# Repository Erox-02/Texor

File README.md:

# Texor
My ultra cool rust based keyboard

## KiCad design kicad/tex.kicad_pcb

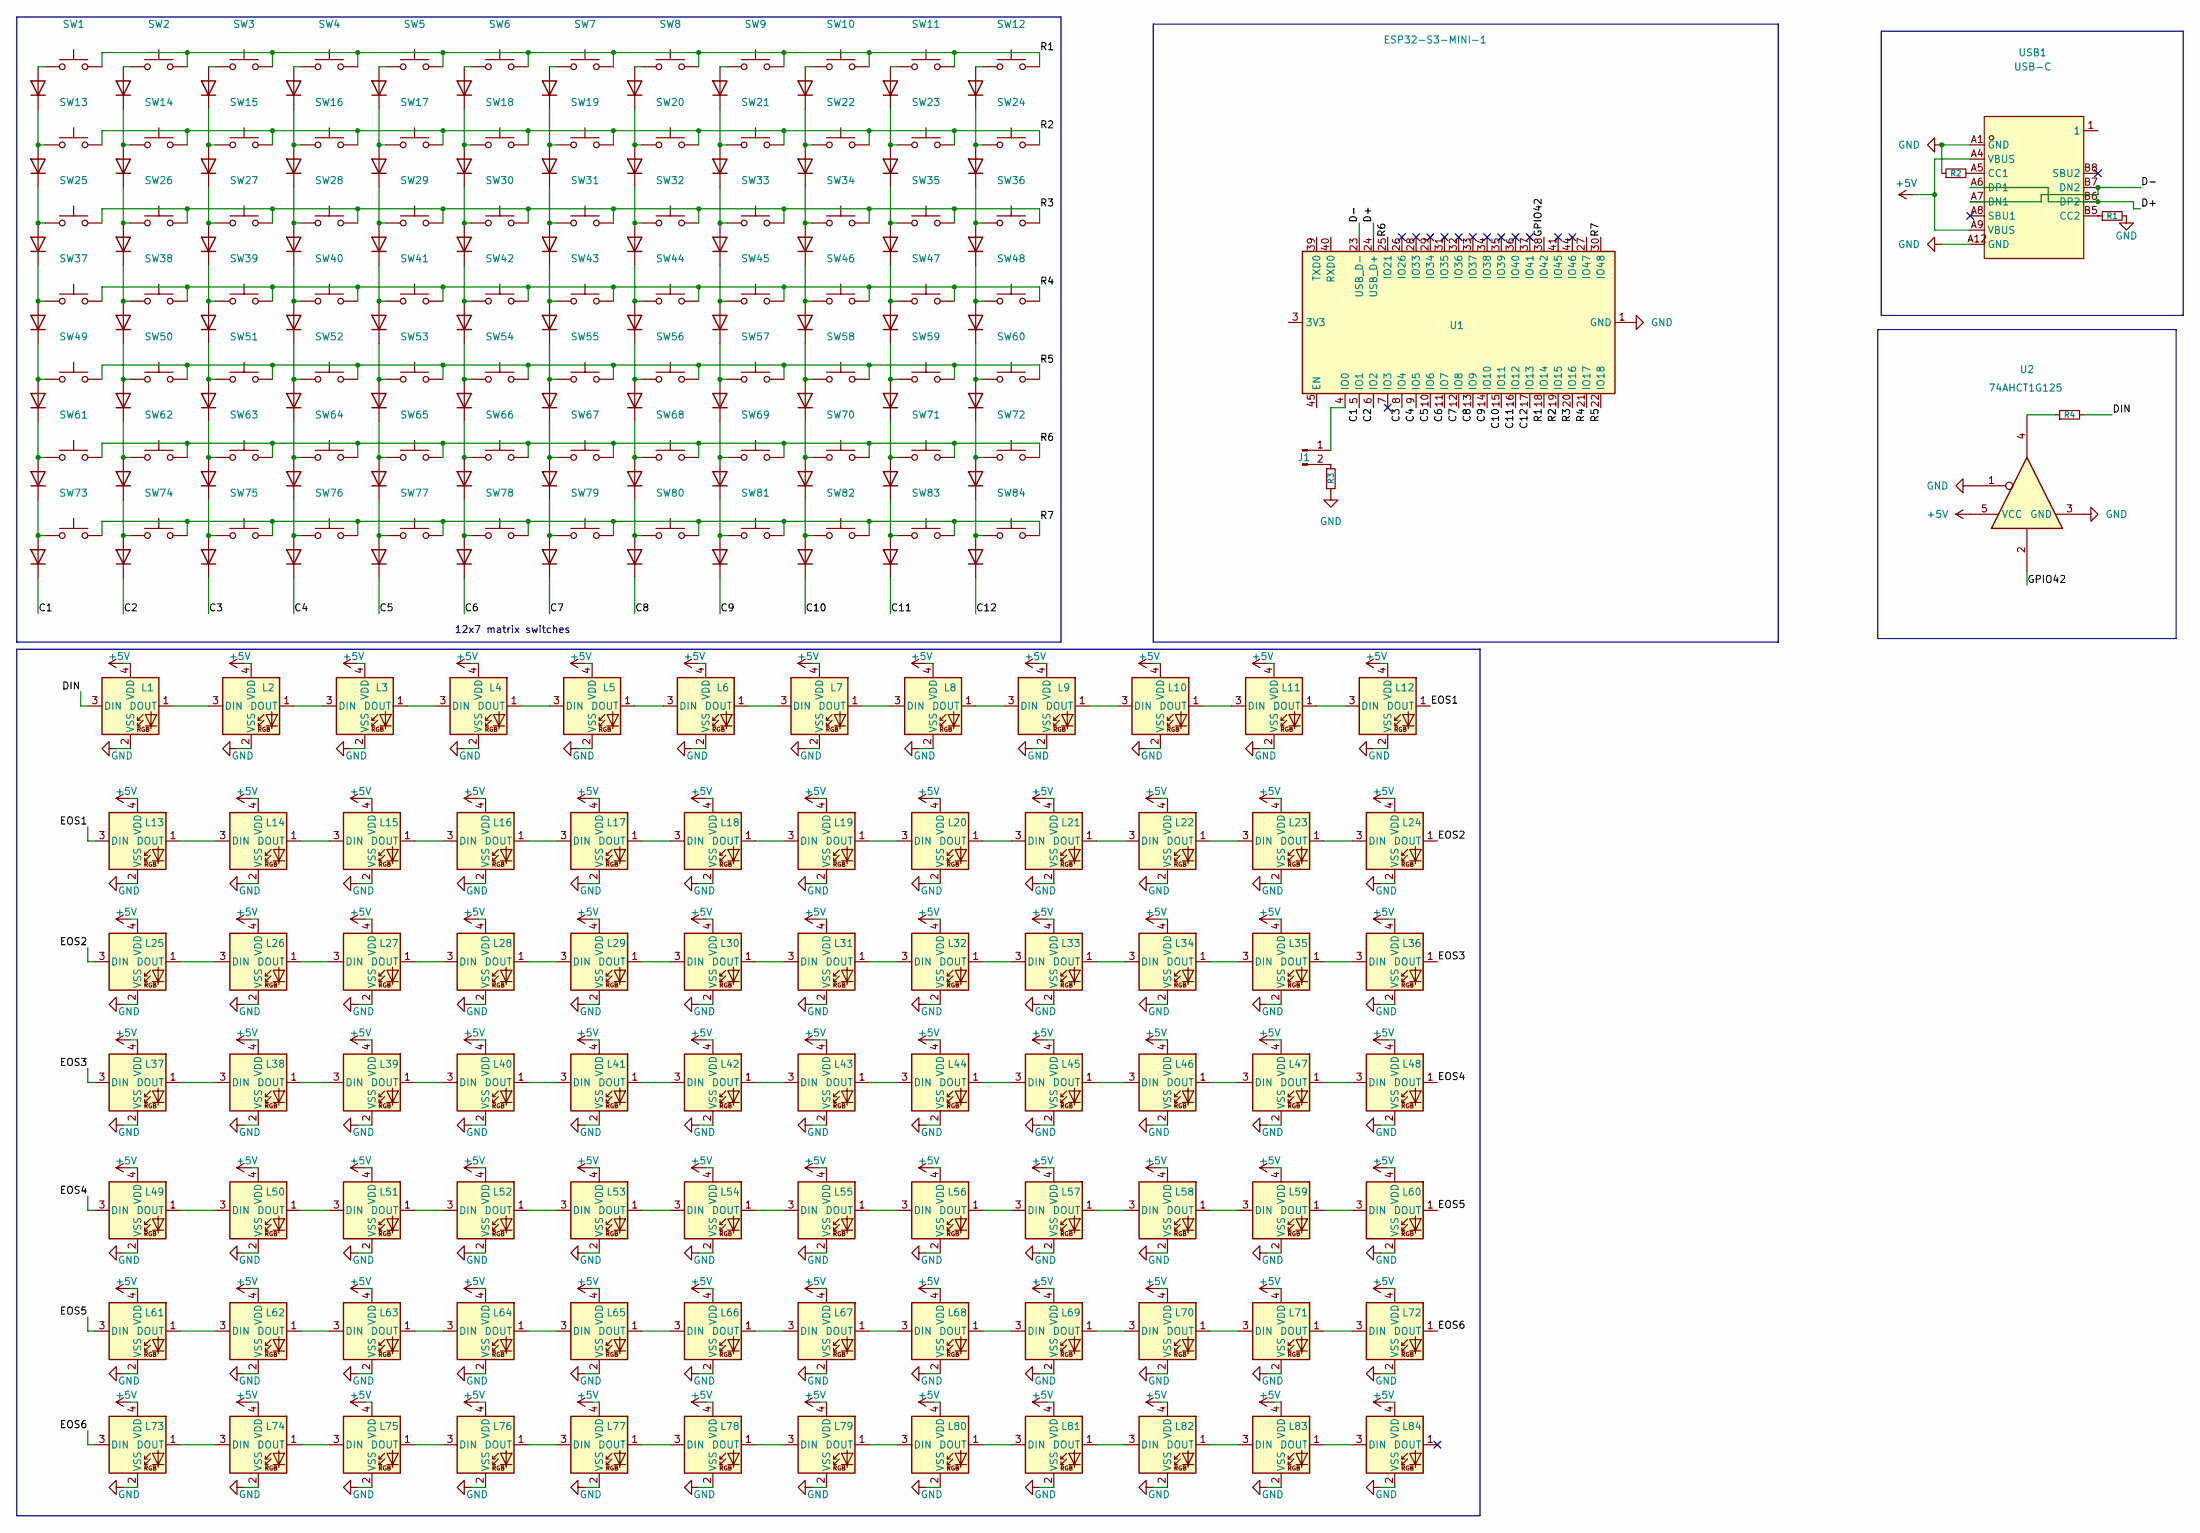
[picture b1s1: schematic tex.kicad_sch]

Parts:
D1, D2, D3, D4, D5, D6, D7, D8, D9, D10, D11, D12, D13, D14, D15, D16, D17, D18, D19, D20, D21, D22, D23, D24, D25, D26, D27, D28, D29, D30, D31, D32, D33, D34, D35, D36, D37, D38, D39, D40, D41, D42, D43, D44, D45, D46, D47, D48, D49, D50, D51, D52, D53, D54, D55, D56, D57, D58, D59, D60, D61, D62, D63, D64, D65, D66, D67, D68, D69, D70, D71, D72, D73, D74, D75, D76, D77, D78, D79, D80, D81, D82, D83, D84: 1N4148W; D_SOD-123
J1: Testpoint; PinSocket_1x02_P2.00mm_Vertical
L1, L2, L3, L4, L5, L6, L7, L8, L9, L10, L11, L12, L13, L14, L15, L16, L17, L18, L19, L20, L21, L22, L23, L24, L25, L26, L27, L28, L29, L30, L31, L32, L33, L34, L35, L36, L37, L38, L39, L40, L41, L42, L43, L44, L45, L46, L47, L48, L49, L50, L51, L52, L53, L54, L55, L56, L57, L58, L59, L60, L61, L62, L63, L64, L65, L66, L67, L68, L69, L70, L71, L72, L73, L74, L75, L76, L77, L78, L79, L80, L81, L82, L83, L84: WS2812B-2020; LED_WS2812B-2020_PLCC4_2.0x2.0mm
R1, R2: 5.1k; R_0603_1608Metric
R3: 10k; R_0603_1608Metric
R4: 220 ohm; R_0603_1608Metric
SW1, SW2, SW3, SW4, SW5, SW6, SW7, SW8, SW9, SW10, SW11, SW12, SW13, SW14, SW15, SW16, SW17, SW18, SW19, SW20, SW21, SW22, SW23, SW24, SW25, SW26, SW27, SW28, SW29, SW30, SW31, SW32, SW33, SW34, SW35, SW36, SW37, SW38, SW39, SW40, SW41, SW42, SW43, SW44, SW45, SW46, SW47, SW48, SW49, SW50, SW51, SW52, SW53, SW54, SW55, SW56, SW57, SW58, SW59, SW60, SW61, SW62, SW63, SW64, SW65, SW66, SW67, SW68, SW69, SW70, SW71, SW72, SW73, SW74, SW75, SW76, SW77, SW78, SW79, SW80, SW81, SW82, SW83, SW84: SW_Push; SW_Cherry_MX_1.00u_PCB
U1: ESP32-S3-MINI-1; ESP32-S2-MINI-1
U2: 74AHCT1G125; SOT-353_SC-70-5
USB1: USB-C; USB-C-SMD_TYPE-C-31-M-31; MPN TYPE-C-31-M-31; LCSC Part C2760486

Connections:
+5V: L1.4 (VDD), L2.4 (VDD), L3.4 (VDD), L4.4 (VDD), L5.4 (VDD), L6.4 (VDD), L7.4 (VDD), L8.4 (VDD), L9.4 (VDD), L10.4 (VDD), L11.4 (VDD), L12.4 (VDD), L13.4 (VDD), L14.4 (VDD), L15.4 (VDD), L16.4 (VDD), L17.4 (VDD), L18.4 (VDD), L19.4 (VDD), L20.4 (VDD), L21.4 (VDD), L22.4 (VDD), L23.4 (VDD), L24.4 (VDD), L25.4 (VDD), L26.4 (VDD), L27.4 (VDD), L28.4 (VDD), L29.4 (VDD), L30.4 (VDD), L31.4 (VDD), L32.4 (VDD), L33.4 (VDD), L34.4 (VDD), L35.4 (VDD), L36.4 (VDD), L37.4 (VDD), L38.4 (VDD), L39.4 (VDD), L40.4 (VDD), L41.4 (VDD), L42.4 (VDD), L43.4 (VDD), L44.4 (VDD), L45.4 (VDD), L46.4 (VDD), L47.4 (VDD), L48.4 (VDD), L49.4 (VDD), L50.4 (VDD), L51.4 (VDD), L52.4 (VDD), L53.4 (VDD), L54.4 (VDD), L55.4 (VDD), L56.4 (VDD), L57.4 (VDD), L58.4 (VDD), L59.4 (VDD), L60.4 (VDD), L61.4 (VDD), L62.4 (VDD), L63.4 (VDD), L64.4 (VDD), L65.4 (VDD), L66.4 (VDD), L67.4 (VDD), L68.4 (VDD), L69.4 (VDD), L70.4 (VDD), L71.4 (VDD), L72.4 (VDD), L73.4 (VDD), L74.4 (VDD), L75.4 (VDD), L76.4 (VDD), L77.4 (VDD), L78.4 (VDD), L79.4 (VDD), L80.4 (VDD), L81.4 (VDD), L82.4 (VDD), L83.4 (VDD), L84.4 (VDD), U2.5 (VCC), USB1.A4 (VBUS), USB1.A9 (VBUS); also elsewhere on the board
/3.3v: U1.3 (3V3); also elsewhere on the board
/C1: D73.1 (K), U1.5 (IO1)
/C2: D74.1 (K), U1.6 (IO2)
/C3: D75.1 (K), U1.8 (IO4)
/C4: D76.1 (K), U1.9 (IO5)
/C5: D77.1 (K), U1.10 (IO6)
/C6: D78.1 (K), U1.11 (IO7)
/C7: D79.1 (K), U1.12 (IO8)
/C8: D80.1 (K), U1.13 (IO9)
/C9: D81.1 (K), U1.14 (IO10)
/C10: D82.1 (K), U1.15 (IO11)
/C11: D83.1 (K), U1.16 (IO12)
/C12: D84.1 (K), U1.17 (IO13)
/D+: U1.24 (USB_D+), USB1.A6 (DP1), USB1.B6 (DP2)
/D-: U1.23 (USB_D-), USB1.A7 (DN1), USB1.B7 (DN2)
/DIN: L1.3 (DIN), R4.2
/EOS1: L12.1 (DOUT), L13.3 (DIN)
/EOS2: L24.1 (DOUT), L25.3 (DIN)
/EOS3: L36.1 (DOUT), L37.3 (DIN)
/EOS4: L48.1 (DOUT), L49.3 (DIN)
/EOS5: L60.1 (DOUT), L61.3 (DIN)
/EOS6: L72.1 (DOUT), L73.3 (DIN)
/GPIO42: U1.38 (IO42), U2.2
/R1: SW1.2, SW2.2, SW3.2, SW4.2, SW5.2, SW6.2, SW7.2, SW8.2, SW9.2, SW10.2, SW11.2, SW12.2, U1.18 (IO14)
/R2: SW13.2, SW14.2, SW15.2, SW16.2, SW17.2, SW18.2, SW19.2, SW20.2, SW21.2, SW22.2, SW23.2, SW24.2, U1.19 (IO15)
/R3: SW25.2, SW26.2, SW27.2, SW28.2, SW29.2, SW30.2, SW31.2, SW32.2, SW33.2, SW34.2, SW35.2, SW36.2, U1.20 (IO16)
/R4: SW37.2, SW38.2, SW39.2, SW40.2, SW41.2, SW42.2, SW43.2, SW44.2, SW45.2, SW46.2, SW47.2, SW48.2, U1.21 (IO17)
/R5: SW49.2, SW50.2, SW51.2, SW52.2, SW53.2, SW54.2, SW55.2, SW56.2, SW57.2, SW58.2, SW59.2, SW60.2, U1.22 (IO18)
/R6: SW61.2, SW62.2, SW63.2, SW64.2, SW65.2, SW66.2, SW67.2, SW68.2, SW69.2, SW70.2, SW71.2, SW72.2, U1.25 (IO21)
/R7: SW73.2, SW74.2, SW75.2, SW76.2, SW77.2, SW78.2, SW79.2, SW80.2, SW81.2, SW82.2, SW83.2, SW84.2, U1.30 (IO48)
GND: L1.2 (VSS), L2.2 (VSS), L3.2 (VSS), L4.2 (VSS), L5.2 (VSS), L6.2 (VSS), L7.2 (VSS), L8.2 (VSS), L9.2 (VSS), L10.2 (VSS), L11.2 (VSS), L12.2 (VSS), L13.2 (VSS), L14.2 (VSS), L15.2 (VSS), L16.2 (VSS), L17.2 (VSS), L18.2 (VSS), L19.2 (VSS), L20.2 (VSS), L21.2 (VSS), L22.2 (VSS), L23.2 (VSS), L24.2 (VSS), L25.2 (VSS), L26.2 (VSS), L27.2 (VSS), L28.2 (VSS), L29.2 (VSS), L30.2 (VSS), L31.2 (VSS), L32.2 (VSS), L33.2 (VSS), L34.2 (VSS), L35.2 (VSS), L36.2 (VSS), L37.2 (VSS), L38.2 (VSS), L39.2 (VSS), L40.2 (VSS), L41.2 (VSS), L42.2 (VSS), L43.2 (VSS), L44.2 (VSS), L45.2 (VSS), L46.2 (VSS), L47.2 (VSS), L48.2 (VSS), L49.2 (VSS), L50.2 (VSS), L51.2 (VSS), L52.2 (VSS), L53.2 (VSS), L54.2 (VSS), L55.2 (VSS), L56.2 (VSS), L57.2 (VSS), L58.2 (VSS), L59.2 (VSS), L60.2 (VSS), L61.2 (VSS), L62.2 (VSS), L63.2 (VSS), L64.2 (VSS), L65.2 (VSS), L66.2 (VSS), L67.2 (VSS), L68.2 (VSS), L69.2 (VSS), L70.2 (VSS), L71.2 (VSS), L72.2 (VSS), L73.2 (VSS), L74.2 (VSS), L75.2 (VSS), L76.2 (VSS), L77.2 (VSS), L78.2 (VSS), L79.2 (VSS), L80.2 (VSS), L81.2 (VSS), L82.2 (VSS), L83.2 (VSS), L84.2 (VSS), R1.2, R2.1, R3.2, U1.1 (GND), U1.2 (GND), U1.42 (GND), U1.43 (GND), U1.46 (GND), U1.47 (GND), U1.48 (GND), U1.49 (GND), U1.50 (GND), U1.51 (GND), U1.52 (GND), U1.53 (GND), U1.54 (GND), U1.55 (GND), U1.56 (GND), U1.57 (GND), U1.58 (GND), U1.59 (GND), U1.60 (GND), U1.61 (GND), U1.62 (GND), U1.63 (GND), U1.64 (GND), U1.65 (GND), U2.1, U2.3 (GND), USB1.A1 (GND), USB1.A12 (GND); also elsewhere on the board
unnamed: D1.2 (A), SW1.1
unnamed: D1.1 (K), D13.2 (A), SW13.1
unnamed: D2.2 (A), SW2.1
unnamed: D3.2 (A), SW3.1
unnamed: D4.2 (A), SW4.1
unnamed: D5.2 (A), SW5.1
unnamed: D6.2 (A), SW6.1
unnamed: D7.2 (A), SW7.1
unnamed: D8.2 (A), SW8.1
unnamed: D9.2 (A), SW9.1
unnamed: D10.2 (A), SW10.1
unnamed: D10.1 (K), D22.2 (A), SW22.1
unnamed: D11.2 (A), SW11.1
unnamed: D11.1 (K), D23.2 (A), SW23.1
unnamed: D12.2 (A), SW12.1
unnamed: D12.1 (K), D24.2 (A), SW24.1
unnamed: D13.1 (K), D25.2 (A), SW25.1
unnamed: D2.1 (K), D14.2 (A), SW14.1
unnamed: D14.1 (K), D26.2 (A), SW26.1
unnamed: D3.1 (K), D15.2 (A), SW15.1
unnamed: D15.1 (K), D27.2 (A), SW27.1
unnamed: D4.1 (K), D16.2 (A), SW16.1
unnamed: D16.1 (K), D28.2 (A), SW28.1
unnamed: D5.1 (K), D17.2 (A), SW17.1
unnamed: D17.1 (K), D29.2 (A), SW29.1
unnamed: D6.1 (K), D18.2 (A), SW18.1
unnamed: D18.1 (K), D30.2 (A), SW30.1
unnamed: D7.1 (K), D19.2 (A), SW19.1
unnamed: D19.1 (K), D31.2 (A), SW31.1
unnamed: D8.1 (K), D20.2 (A), SW20.1
unnamed: D20.1 (K), D32.2 (A), SW32.1
unnamed: D9.1 (K), D21.2 (A), SW21.1
unnamed: D21.1 (K), D33.2 (A), SW33.1
unnamed: D22.1 (K), D34.2 (A), SW34.1
unnamed: D23.1 (K), D35.2 (A), SW35.1
unnamed: D24.1 (K), D36.2 (A), SW36.1
unnamed: D25.1 (K), D37.2 (A), SW37.1
unnamed: D26.1 (K), D38.2 (A), SW38.1
unnamed: D27.1 (K), D39.2 (A), SW39.1
unnamed: D28.1 (K), D40.2 (A), SW40.1
unnamed: D29.1 (K), D41.2 (A), SW41.1
unnamed: D30.1 (K), D42.2 (A), SW42.1
unnamed: D31.1 (K), D43.2 (A), SW43.1
unnamed: D32.1 (K), D44.2 (A), SW44.1
unnamed: D33.1 (K), D45.2 (A), SW45.1
unnamed: D34.1 (K), D46.2 (A), SW46.1
unnamed: D35.1 (K), D47.2 (A), SW47.1
unnamed: D36.1 (K), D48.2 (A), SW48.1
unnamed: D37.1 (K), D49.2 (A), SW49.1
unnamed: D38.1 (K), D50.2 (A), SW50.1
unnamed: D39.1 (K), D51.2 (A), SW51.1
unnamed: D40.1 (K), D52.2 (A), SW52.1
unnamed: D41.1 (K), D53.2 (A), SW53.1
unnamed: D42.1 (K), D54.2 (A), SW54.1
unnamed: D43.1 (K), D55.2 (A), SW55.1
unnamed: D44.1 (K), D56.2 (A), SW56.1
unnamed: D45.1 (K), D57.2 (A), SW57.1
unnamed: D46.1 (K), D58.2 (A), SW58.1
unnamed: D47.1 (K), D59.2 (A), SW59.1
unnamed: D48.1 (K), D60.2 (A), SW60.1
unnamed: D49.1 (K), D61.2 (A), SW61.1
unnamed: D50.1 (K), D62.2 (A), SW62.1
unnamed: D51.1 (K), D63.2 (A), SW63.1
unnamed: D52.1 (K), D64.2 (A), SW64.1
unnamed: D53.1 (K), D65.2 (A), SW65.1
unnamed: D54.1 (K), D66.2 (A), SW66.1
unnamed: D55.1 (K), D67.2 (A), SW67.1
unnamed: D56.1 (K), D68.2 (A), SW68.1
unnamed: D57.1 (K), D69.2 (A), SW69.1
unnamed: D58.1 (K), D70.2 (A), SW70.1
unnamed: D59.1 (K), D71.2 (A), SW71.1
unnamed: D60.1 (K), D72.2 (A), SW72.1
unnamed: D61.1 (K), D73.2 (A), SW73.1
unnamed: D62.1 (K), D74.2 (A), SW74.1
unnamed: D63.1 (K), D75.2 (A), SW75.1
unnamed: D64.1 (K), D76.2 (A), SW76.1
unnamed: D65.1 (K), D77.2 (A), SW77.1
unnamed: D66.1 (K), D78.2 (A), SW78.1
unnamed: D67.1 (K), D79.2 (A), SW79.1
unnamed: D68.1 (K), D80.2 (A), SW80.1
unnamed: D69.1 (K), D81.2 (A), SW81.1
unnamed: D70.1 (K), D82.2 (A), SW82.1
unnamed: D71.1 (K), D83.2 (A), SW83.1
unnamed: D72.1 (K), D84.2 (A), SW84.1
unnamed: J1.1, U1.4 (IO0)
unnamed: J1.2, R3.1
unnamed: L1.1 (DOUT), L2.3 (DIN)
unnamed: L2.1 (DOUT), L3.3 (DIN)
unnamed: L3.1 (DOUT), L4.3 (DIN)
unnamed: L4.1 (DOUT), L5.3 (DIN)
unnamed: L5.1 (DOUT), L6.3 (DIN)
unnamed: L6.1 (DOUT), L7.3 (DIN)
unnamed: L7.1 (DOUT), L8.3 (DIN)
unnamed: L8.1 (DOUT), L9.3 (DIN)
unnamed: L9.1 (DOUT), L10.3 (DIN)
unnamed: L10.1 (DOUT), L11.3 (DIN)
unnamed: L11.1 (DOUT), L12.3 (DIN)
unnamed: L13.1 (DOUT), L14.3 (DIN)
unnamed: L14.1 (DOUT), L15.3 (DIN)
unnamed: L15.1 (DOUT), L16.3 (DIN)
unnamed: L16.1 (DOUT), L17.3 (DIN)
unnamed: L17.1 (DOUT), L18.3 (DIN)
unnamed: L18.1 (DOUT), L19.3 (DIN)
unnamed: L19.1 (DOUT), L20.3 (DIN)
unnamed: L20.1 (DOUT), L21.3 (DIN)
unnamed: L21.1 (DOUT), L22.3 (DIN)
unnamed: L22.1 (DOUT), L23.3 (DIN)
unnamed: L23.1 (DOUT), L24.3 (DIN)
unnamed: L25.1 (DOUT), L26.3 (DIN)
unnamed: L26.1 (DOUT), L27.3 (DIN)
unnamed: L27.1 (DOUT), L28.3 (DIN)
unnamed: L28.1 (DOUT), L29.3 (DIN)
unnamed: L29.1 (DOUT), L30.3 (DIN)
unnamed: L30.1 (DOUT), L31.3 (DIN)
unnamed: L31.1 (DOUT), L32.3 (DIN)
unnamed: L32.1 (DOUT), L33.3 (DIN)
unnamed: L33.1 (DOUT), L34.3 (DIN)
unnamed: L34.1 (DOUT), L35.3 (DIN)
unnamed: L35.1 (DOUT), L36.3 (DIN)
unnamed: L37.1 (DOUT), L38.3 (DIN)
unnamed: L38.1 (DOUT), L39.3 (DIN)
unnamed: L39.1 (DOUT), L40.3 (DIN)
unnamed: L40.1 (DOUT), L41.3 (DIN)
unnamed: L41.1 (DOUT), L42.3 (DIN)
unnamed: L42.1 (DOUT), L43.3 (DIN)
unnamed: L43.1 (DOUT), L44.3 (DIN)
unnamed: L44.1 (DOUT), L45.3 (DIN)
unnamed: L45.1 (DOUT), L46.3 (DIN)
unnamed: L46.1 (DOUT), L47.3 (DIN)
unnamed: L47.1 (DOUT), L48.3 (DIN)
unnamed: L49.1 (DOUT), L50.3 (DIN)
unnamed: L50.1 (DOUT), L51.3 (DIN)
unnamed: L51.1 (DOUT), L52.3 (DIN)
unnamed: L52.1 (DOUT), L53.3 (DIN)
unnamed: L53.1 (DOUT), L54.3 (DIN)
unnamed: L54.1 (DOUT), L55.3 (DIN)
unnamed: L55.1 (DOUT), L56.3 (DIN)
unnamed: L56.1 (DOUT), L57.3 (DIN)
unnamed: L57.1 (DOUT), L58.3 (DIN)
unnamed: L58.1 (DOUT), L59.3 (DIN)
unnamed: L59.1 (DOUT), L60.3 (DIN)
unnamed: L61.1 (DOUT), L62.3 (DIN)
unnamed: L62.1 (DOUT), L63.3 (DIN)
unnamed: L63.1 (DOUT), L64.3 (DIN)
unnamed: L64.1 (DOUT), L65.3 (DIN)
unnamed: L65.1 (DOUT), L66.3 (DIN)
unnamed: L66.1 (DOUT), L67.3 (DIN)
unnamed: L67.1 (DOUT), L68.3 (DIN)
unnamed: L68.1 (DOUT), L69.3 (DIN)
unnamed: L69.1 (DOUT), L70.3 (DIN)
unnamed: L70.1 (DOUT), L71.3 (DIN)
unnamed: L71.1 (DOUT), L72.3 (DIN)
unnamed: L73.1 (DOUT), L74.3 (DIN)
unnamed: L74.1 (DOUT), L75.3 (DIN)
unnamed: L75.1 (DOUT), L76.3 (DIN)
unnamed: L76.1 (DOUT), L77.3 (DIN)
unnamed: L77.1 (DOUT), L78.3 (DIN)
unnamed: L78.1 (DOUT), L79.3 (DIN)
unnamed: L79.1 (DOUT), L80.3 (DIN)
unnamed: L80.1 (DOUT), L81.3 (DIN)
unnamed: L81.1 (DOUT), L82.3 (DIN)
unnamed: L82.1 (DOUT), L83.3 (DIN)
unnamed: L83.1 (DOUT), L84.3 (DIN)
unnamed: R4.1, U2.4
unnamed: R2.2, USB1.A5 (CC1)
unnamed: R1.1, USB1.B5 (CC2)

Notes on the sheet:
12x7 matrix switches

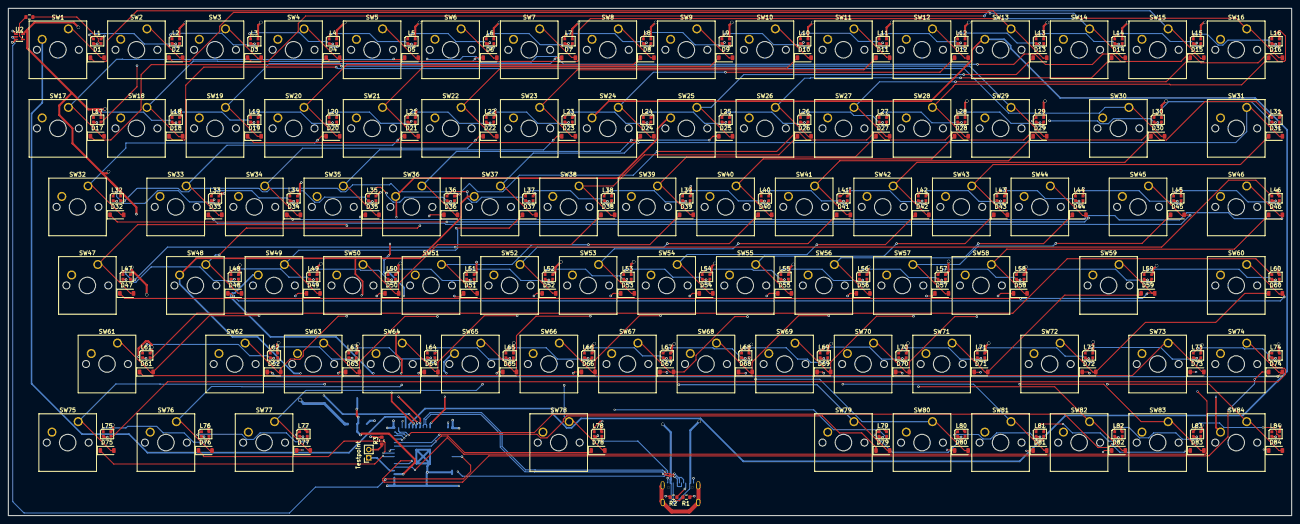
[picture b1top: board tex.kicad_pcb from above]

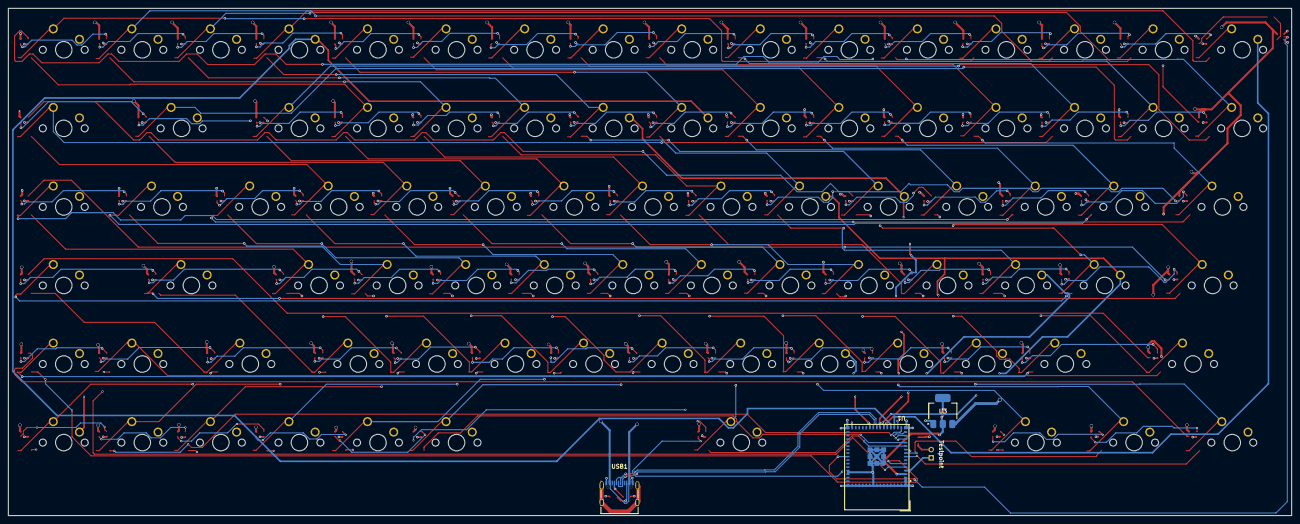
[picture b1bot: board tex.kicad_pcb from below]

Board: 4 copper layers, 311.2 x 123.0 mm, 261 parts (3 on the bottom side), 198 nets.

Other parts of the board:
U3: AMS1117; SOT-223-3_TabPin2

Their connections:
+5V: U3.3 (VI); also elsewhere on the board
/3.3v: U3.2 (VO); also elsewhere on the board
GND: U3.1 (ADJ); also elsewhere on the board
